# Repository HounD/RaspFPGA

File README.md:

RaspFPGA
========

RaspFPGA mezzanine board for Raspberry Pi

It's not mine, but saved from here for the future use:
http://mbecho.blogspot.it/2013/09/raspfpga-mezzanine-board-for-raspberry.html

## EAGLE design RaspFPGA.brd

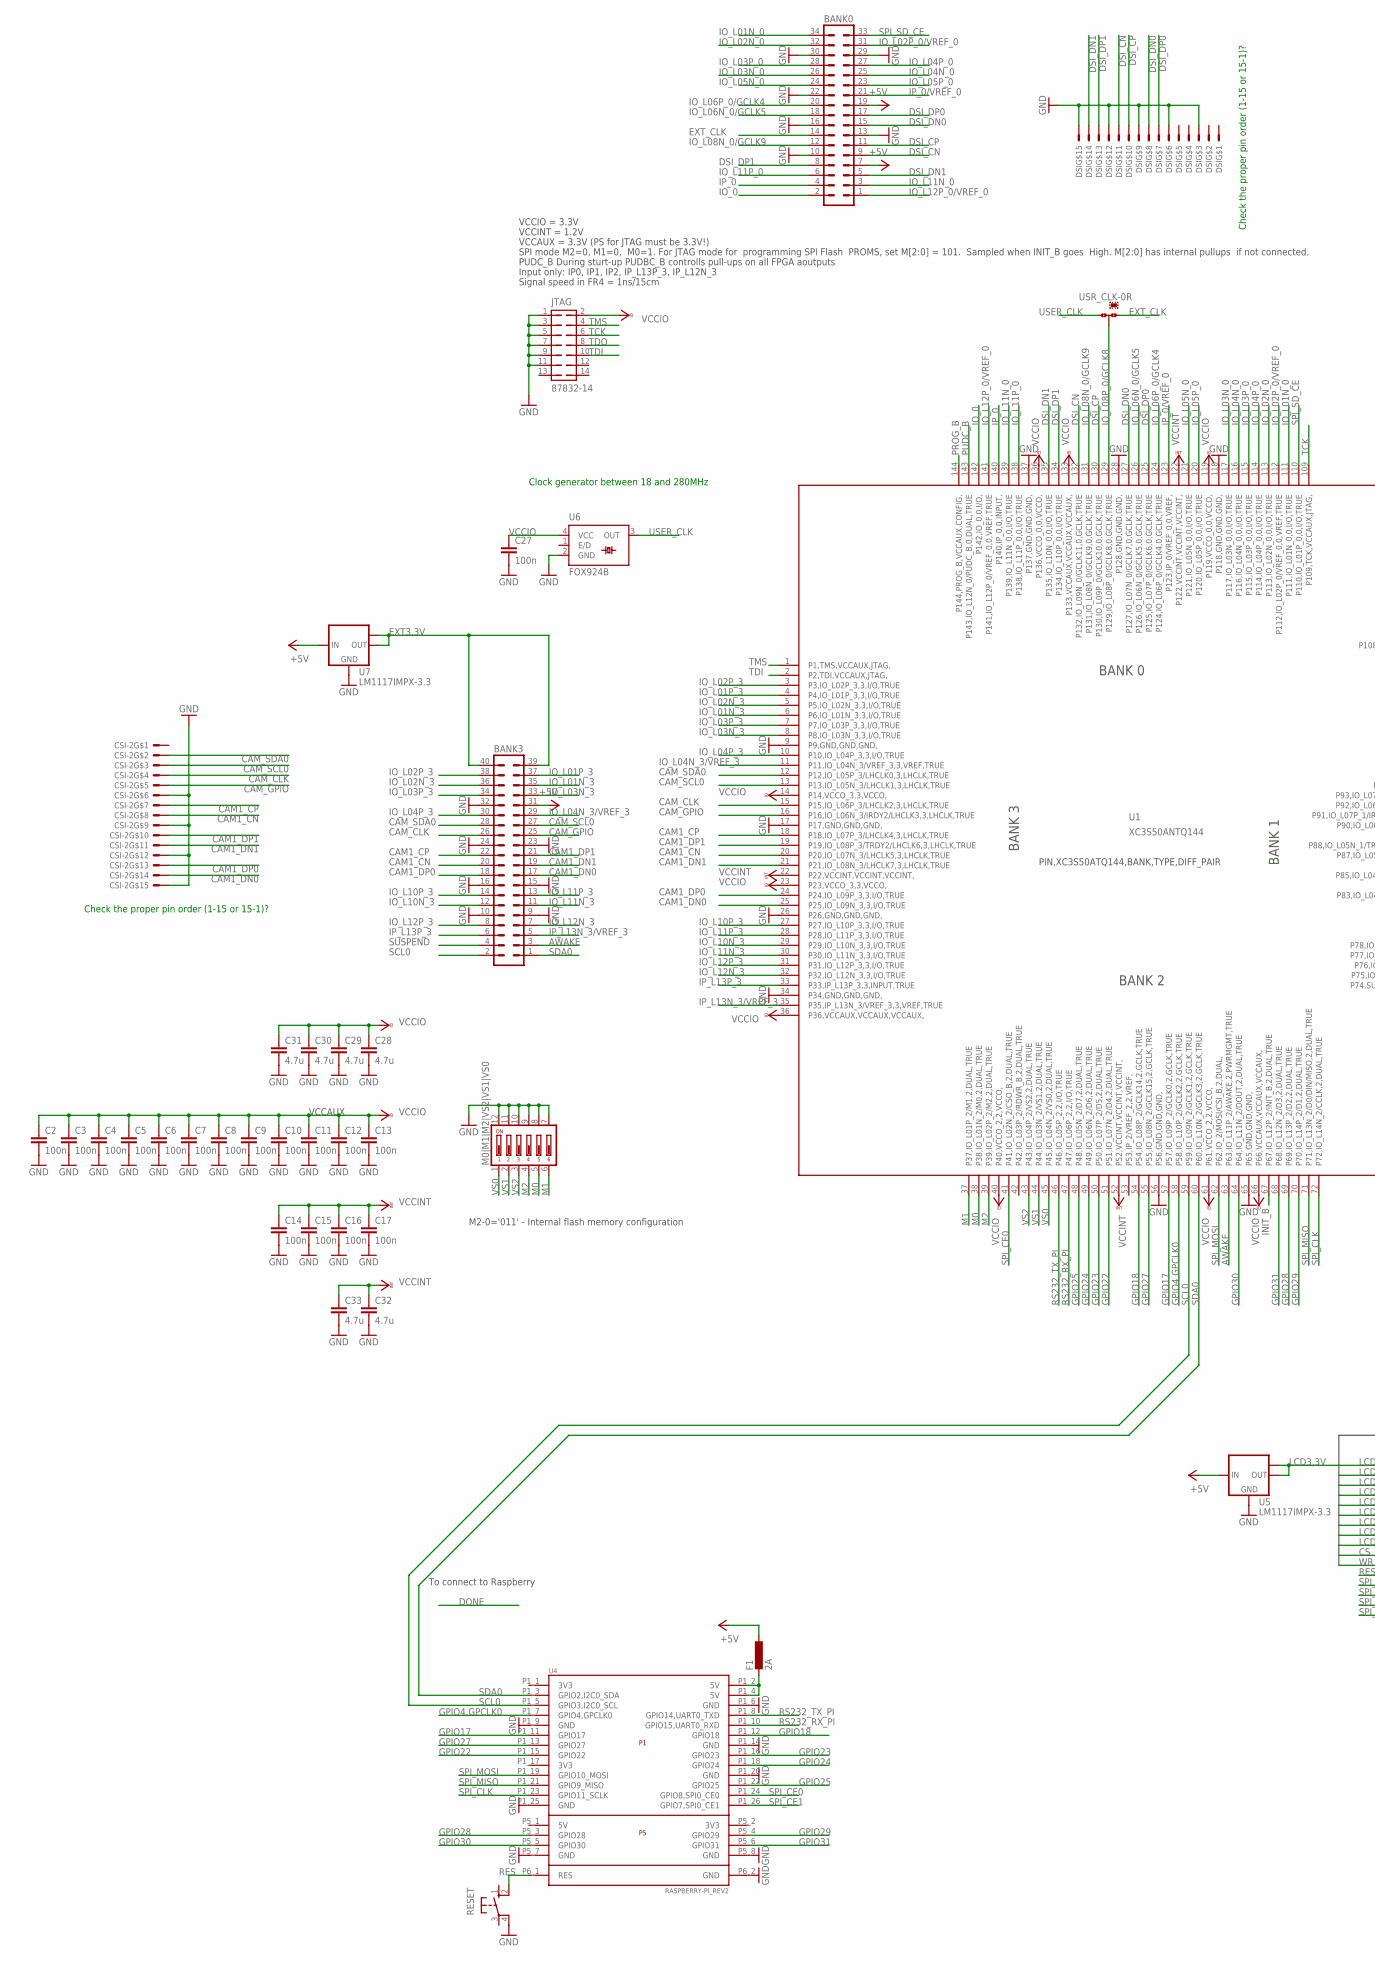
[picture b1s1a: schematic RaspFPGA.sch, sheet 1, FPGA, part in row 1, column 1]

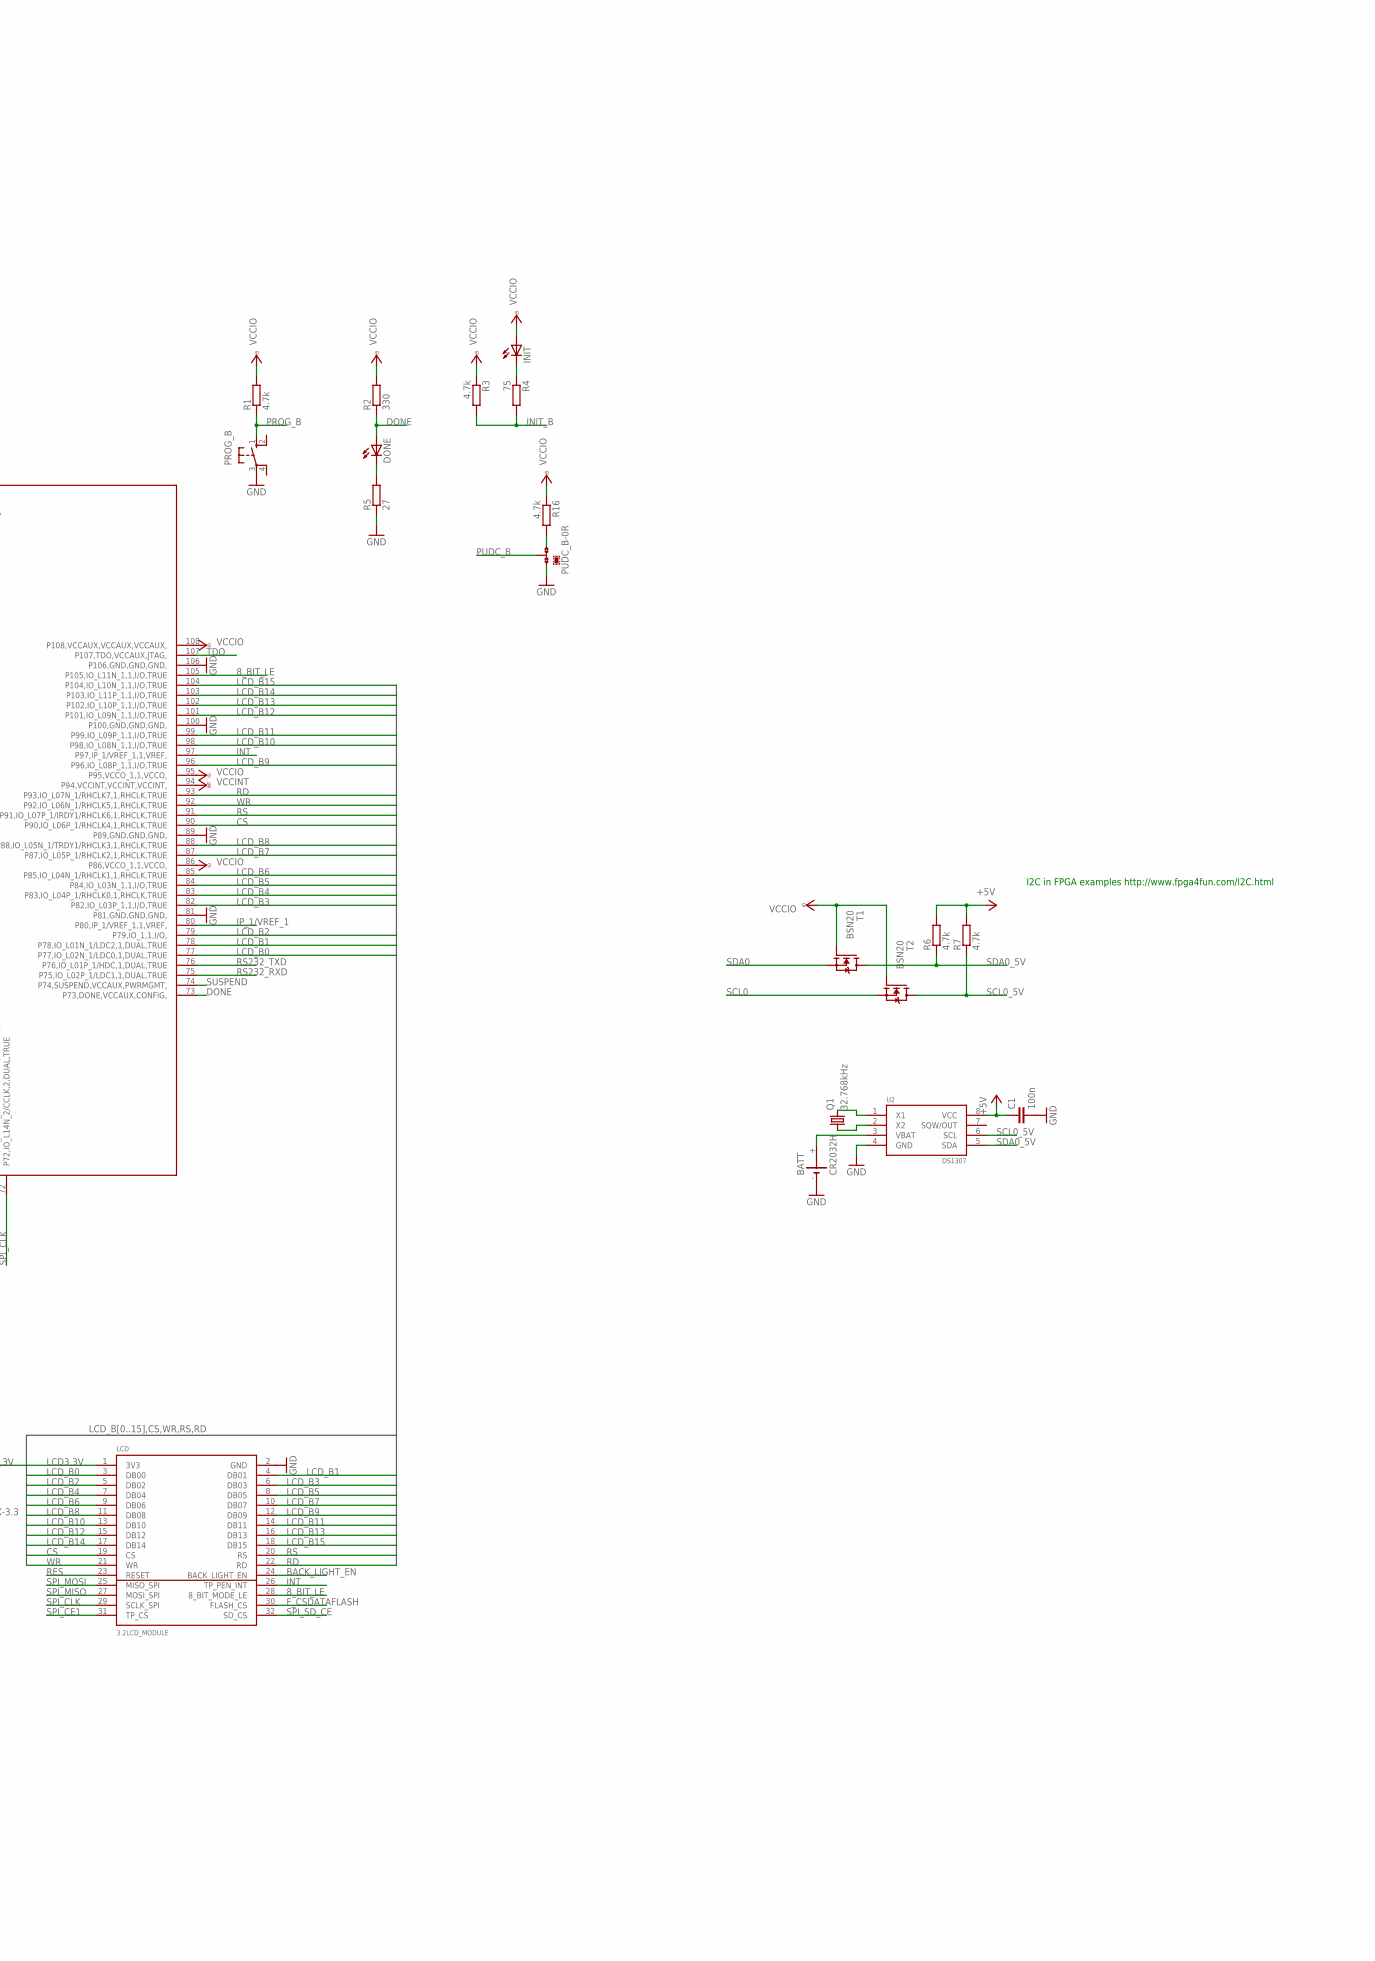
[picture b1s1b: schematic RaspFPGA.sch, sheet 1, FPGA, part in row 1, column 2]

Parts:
BANK0: MA17-2W
BANK3: MA20-2W
BATT: CR2032H
C1, C2, C3, C4, C5, C6, C7, C8, C9, C10, C11, C12, C13, C14, C15, C16, C17, C27: 100n; C0603
C28, C29, C30, C31, C32, C33: 4.7u; C0603
CSI-2: 52271-1579
DONE: LEDCHIP-LED0603; CHIP-LED0603
DSI: 52271-1579
F1: 2A; L1812
INIT: LEDCHIP-LED0603; CHIP-LED0603
JTAG: 87832-14
LCD: 3.2LCD_MODULE
M0|M1|M2|VS2|VS1|VS0: DIP06YL
PROG_B: 10-XX; B3F-10XX
PUDC_B: 0R-JUMPA; A0R-JMP
Q1: 32.768kHz; TC38H
R1, R3, R6, R7, R16: 4.7k; R0603
R2: 330; R0603
R4: 75; R0603
R5: 27; R0603
RESET: 10-XX; B3F-10XX
T1, T2: BSN20; SOT23
U1: XC3S50ANTQ144; TQ144
U2: DS1307; SO8
U4: RASPBERRY-PI_REV2
U5, U7: LM1117IMPX-3.3; SOT223
U6: FOX924B
USR_CLK: 0R-JUMPA; A0R-JMP

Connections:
8_BIT_LE: LCD.28 (8_BIT_MODE_LE), U1.105 (P105,IO_L11N_1,1,I/O,TRUE)
+5V: BANK0.7, BANK0.19, BANK3.31, C1.1, F1.1, R6.2, R7.2, U2.8 (VCC), U5.3 (IN), U7.3 (IN); also elsewhere on the board
AWAKE: BANK3.3, U1.63 (P63,IO_L11P_2/AWAKE,2,PWRMGMT,TRUE)
BACK_LIGHT_EN: LCD.24 (BACK_LIGHT_EN)
CAM1_CN: BANK3.20, CSI-2.P$8, U1.20 (P20,IO_L07N_3/LHCLK5,3,LHCLK,TRUE)
CAM1_CP: BANK3.22, CSI-2.P$7, U1.18 (P18,IO_L07P_3/LHCLK4,3,LHCLK,TRUE)
CAM1_DN0: BANK3.17, CSI-2.P$14, U1.25 (P25,IO_L09N_3,3,I/O,TRUE)
CAM1_DN1: BANK3.19, CSI-2.P$11, U1.21 (P21,IO_L08N_3/LHCLK7,3,LHCLK,TRUE)
CAM1_DP0: BANK3.18, CSI-2.P$13, U1.24 (P24,IO_L09P_3,3,I/O,TRUE)
CAM1_DP1: BANK3.21, CSI-2.P$10, U1.19 (P19,IO_L08P_3/TRDY2/LHCLK6,3,LHCLK,TRUE)
CAM_CLK: BANK3.26, CSI-2.P$4, U1.15 (P15,IO_L06P_3/LHCLK2,3,LHCLK,TRUE)
CAM_GPIO: BANK3.25, CSI-2.P$5, U1.16 (P16,IO_L06N_3/IRDY2/LHCLK3,3,LHCLK,TRUE)
CAM_SCL0: BANK3.27, CSI-2.P$3, U1.13 (P13,IO_L05N_3/LHCLK1,3,LHCLK,TRUE)
CAM_SDA0: BANK3.28, CSI-2.P$2, U1.12 (P12,IO_L05P_3/LHCLK0,3,LHCLK,TRUE)
CS: LCD.19 (CS), U1.90 (P90,IO_L06P_1/RHCLK4,1,RHCLK,TRUE)
DONE: DONE.A, R2.1, U1.73 (P73,DONE,VCCAUX,CONFIG,)
DSI_CN: BANK0.9, DSI.P$11, U1.132 (P132,IO_L09N_0/GCLK11,0,GCLK,TRUE)
DSI_CP: BANK0.11, DSI.P$10, U1.130 (P130,IO_L09P_0/GCLK10,0,GCLK,TRUE)
DSI_DN0: BANK0.15, DSI.P$8, U1.127 (P127,IO_L07N_0/GCLK7,0,GCLK,TRUE)
DSI_DN1: BANK0.5, DSI.P$14, U1.135 (P135,IO_L10N_0,0,I/O,TRUE)
DSI_DP0: BANK0.17, DSI.P$7, U1.125 (P125,IO_L07P_0/GCLK6,0,GCLK,TRUE)
DSI_DP1: BANK0.8, DSI.P$13, U1.134 (P134,IO_L10P_0,0,I/O,TRUE)
EXT3,3V: BANK3.39, BANK3.40, U7.2 (OUT), U7.TAB (OUT1)
EXT_CLK: BANK0.14, USR_CLK.1
F_CSDATAFLASH: LCD.30 (FLASH_CS)
GND: BANK0.10, BANK0.13, BANK0.16, BANK0.22, BANK0.29, BANK0.30, BANK3.9, BANK3.10, BANK3.15, BANK3.16, BANK3.23, BANK3.24, BANK3.32, BATT.-, C1.2, C2.2, C3.2, C4.2, C5.2, C6.2, C7.2, C8.2, C9.2, C10.2, C11.2, C12.2, C13.2, C14.2, C15.2, C16.2, C17.2, C27.2, C28.2, C29.2, C30.2, C31.2, C32.2, C33.2, CSI-2.P$6, CSI-2.P$9, CSI-2.P$12, CSI-2.P$15, DSI.P$3, DSI.P$6, DSI.P$9, DSI.P$12, DSI.P$15, JTAG.1, JTAG.3, JTAG.5, JTAG.7, JTAG.9, JTAG.11, LCD.2 (GND), M0|M1|M2|VS2|VS1|VS0.7, M0|M1|M2|VS2|VS1|VS0.8, M0|M1|M2|VS2|VS1|VS0.9, M0|M1|M2|VS2|VS1|VS0.10, M0|M1|M2|VS2|VS1|VS0.11, M0|M1|M2|VS2|VS1|VS0.12, PROG_B.3, PUDC_B.1, R5.1, RESET.4 (P1), U1.9 (P9,GND,GND,GND,), U1.17 (P17,GND,GND,GND,), U1.26 (P26,GND,GND,GND,), U1.34 (P34,GND,GND,GND,), U1.56 (P56,GND,GND,GND,), U1.65 (P65,GND,GND,GND,), U1.81 (P81,GND,GND,GND,), U1.89 (P89,GND,GND,GND,), U1.100 (P100,GND,GND,GND,), U1.106 (P106,GND,GND,GND,), U1.118 (P118,GND,GND,GND,), U1.128 (P128,GND,GND,GND,), U1.137 (P137,GND,GND,GND,), U2.4 (GND), U4.P1_6 (GND), U4.P1_9 (GND), U4.P1_14 (GND), U4.P1_20 (GND), U4.P1_25 (GND), U4.P5_7 (GND), U4.P5_8 (GND), U4.P6_2 (GND), U5.1 (GND), U6.2 (GND), U7.1 (GND); also elsewhere on the board
GPIO4,GPCLK0: U1.58 (P58,IO_L10P_2/GCLK2,2,GCLK,TRUE), U4.P1_7 (GPIO4,GPCLK0)
GPIO17: U1.57 (P57,IO_L09P_2/GCLK0,2,GCLK,TRUE), U4.P1_11 (GPIO17)
GPIO18: U1.54 (P54,IO_L08P_2/GCLK14,2,GCLK,TRUE), U4.P1_12 (GPIO18)
GPIO22: U1.51 (P51,IO_L07N_2/D4,2,DUAL,TRUE), U4.P1_15 (GPIO22)
GPIO23: U1.50 (P50,IO_L07P_2/D5,2,DUAL,TRUE), U4.P1_16 (GPIO23)
GPIO24: U1.49 (P49,IO_L06N_2/D6,2,DUAL,TRUE), U4.P1_18 (GPIO24)
GPIO25: U1.48 (P48,IO_L05N_2/D7,2,DUAL,TRUE), U4.P1_22 (GPIO25)
GPIO27: U1.55 (P55,IO_L08N_2/GCLK15,2,GCLK,TRUE), U4.P1_13 (GPIO27)
GPIO28: U1.69 (P69,IO_L13P_2/D2,2,DUAL,TRUE), U4.P5_3 (GPIO28)
GPIO29: U1.70 (P70,IO_L14P_2/D1,2,DUAL,TRUE), U4.P5_4 (GPIO29)
GPIO30: U1.64 (P64,IO_L11N_2/DOUT,2,DUAL,TRUE), U4.P5_5 (GPIO30)
GPIO31: U1.68 (P68,IO_L12N_2/D3,2,DUAL,TRUE), U4.P5_6 (GPIO31)
INIT: INIT.C, R4.1
INIT_B: R3.2, R4.2, U1.67 (P67,IO_L12P_2/INIT_B,2,DUAL,TRUE)
INT: LCD.26 (TP_PEN_INT), U1.97 (P97,IP_1/VREF_1,1,VREF,)
IO_0: BANK0.2, U1.142 (P142,IO_0,0,I/O,)
IO_L01N_0: BANK0.34, U1.111 (P111,IO_L01N_0,0,I/O,TRUE)
IO_L01N_3: BANK3.35, U1.6 (P6,IO_L01N_3,3,I/O,TRUE)
IO_L01P_3: BANK3.37, U1.4 (P4,IO_L01P_3,3,I/O,TRUE)
IO_L02N_0: BANK0.32, U1.113 (P113,IO_L02N_0,0,I/O,TRUE)
IO_L02N_3: BANK3.36, U1.5 (P5,IO_L02N_3,3,I/O,TRUE)
IO_L02P_0/VREF_0: BANK0.31, U1.112 (P112,IO_L02P_0/VREF_0,0,VREF,TRUE)
IO_L02P_3: BANK3.38, U1.3 (P3,IO_L02P_3,3,I/O,TRUE)
IO_L03N_0: BANK0.26, U1.117 (P117,IO_L03N_0,0,I/O,TRUE)
IO_L03N_3: BANK3.33, U1.8 (P8,IO_L03N_3,3,I/O,TRUE)
IO_L03P_0: BANK0.28, U1.115 (P115,IO_L03P_0,0,I/O,TRUE)
IO_L03P_3: BANK3.34, U1.7 (P7,IO_L03P_3,3,I/O,TRUE)
IO_L04N_0: BANK0.25, U1.116 (P116,IO_L04N_0,0,I/O,TRUE)
IO_L04N_3/VREF_3: BANK3.29, U1.11 (P11,IO_L04N_3/VREF_3,3,VREF,TRUE)
IO_L04P_0: BANK0.27, U1.114 (P114,IO_L04P_0,0,I/O,TRUE)
IO_L04P_3: BANK3.30, U1.10 (P10,IO_L04P_3,3,I/O,TRUE)
IO_L05N_0: BANK0.24, U1.121 (P121,IO_L05N_0,0,I/O,TRUE)
IO_L05P_0: BANK0.23, U1.120 (P120,IO_L05P_0,0,I/O,TRUE)
IO_L06N_0/GCLK5: BANK0.18, U1.126 (P126,IO_L06N_0/GCLK5,0,GCLK,TRUE)
IO_L06P_0/GCLK4: BANK0.20, U1.124 (P124,IO_L06P_0/GCLK4,0,GCLK,TRUE)
IO_L08N_0/GCLK9: BANK0.12, U1.131 (P131,IO_L08N_0/GCLK9,0,GCLK,TRUE)
IO_L08P_0/GCLK8: U1.129 (P129,IO_L08P_0/GCLK8,0,GCLK,TRUE), USR_CLK.2
IO_L10N_3: BANK3.12, U1.29 (P29,IO_L10N_3,3,I/O,TRUE)
IO_L10P_3: BANK3.14, U1.27 (P27,IO_L10P_3,3,I/O,TRUE)
IO_L11N_0: BANK0.3, U1.139 (P139,IO_L11N_0,0,I/O,TRUE)
IO_L11N_3: BANK3.11, U1.30 (P30,IO_L11N_3,3,I/O,TRUE)
IO_L11P_0: BANK0.6, U1.138 (P138,IO_L11P_0,0,I/O,TRUE)
IO_L11P_3: BANK3.13, U1.28 (P28,IO_L11P_3,3,I/O,TRUE)
IO_L12N_3: BANK3.7, U1.32 (P32,IO_L12N_3,3,I/O,TRUE)
IO_L12P_0/VREF_0: BANK0.1, U1.141 (P141,IO_L12P_0/VREF_0,0,VREF,TRUE)
IO_L12P_3: BANK3.8, U1.31 (P31,IO_L12P_3,3,I/O,TRUE)
IP_0: BANK0.4, U1.140 (P140,IP_0,0,INPUT,)
IP_0/VREF_0: BANK0.21, U1.123 (P123,IP_0/VREF_0,0,VREF,)
IP_1/VREF_1: U1.80 (P80,IP_1/VREF_1,1,VREF,)
IP_L13N_3/VREF_3: BANK3.5, U1.35 (P35,IP_L13N_3/VREF_3,3,VREF,TRUE)
IP_L13P_3: BANK3.6, U1.33 (P33,IP_L13P_3,3,INPUT,TRUE)
LCD3,3V: LCD.1 (3V3), U5.2 (OUT), U5.TAB (OUT1)
LCD_B0: LCD.3 (DB00), U1.77 (P77,IO_L02N_1/LDC0,1,DUAL,TRUE)
LCD_B1: LCD.4 (DB01), U1.78 (P78,IO_L01N_1/LDC2,1,DUAL,TRUE)
LCD_B2: LCD.5 (DB02), U1.79 (P79,IO_1,1,I/O,)
LCD_B3: LCD.6 (DB03), U1.82 (P82,IO_L03P_1,1,I/O,TRUE)
LCD_B4: LCD.7 (DB04), U1.83 (P83,IO_L04P_1/RHCLK0,1,RHCLK,TRUE)
LCD_B5: LCD.8 (DB05), U1.84 (P84,IO_L03N_1,1,I/O,TRUE)
LCD_B6: LCD.9 (DB06), U1.85 (P85,IO_L04N_1/RHCLK1,1,RHCLK,TRUE)
LCD_B7: LCD.10 (DB07), U1.87 (P87,IO_L05P_1/RHCLK2,1,RHCLK,TRUE)
LCD_B8: LCD.11 (DB08), U1.88 (P88,IO_L05N_1/TRDY1/RHCLK3,1,RHCLK,TRUE)
LCD_B9: LCD.12 (DB09), U1.96 (P96,IO_L08P_1,1,I/O,TRUE)
LCD_B10: LCD.13 (DB10), U1.98 (P98,IO_L08N_1,1,I/O,TRUE)
LCD_B11: LCD.14 (DB11), U1.99 (P99,IO_L09P_1,1,I/O,TRUE)
LCD_B12: LCD.15 (DB12), U1.101 (P101,IO_L09N_1,1,I/O,TRUE)
LCD_B13: LCD.16 (DB13), U1.102 (P102,IO_L10P_1,1,I/O,TRUE)
LCD_B14: LCD.17 (DB14), U1.103 (P103,IO_L11P_1,1,I/O,TRUE)
LCD_B15: LCD.18 (DB15), U1.104 (P104,IO_L10N_1,1,I/O,TRUE)
M0: M0|M1|M2|VS2|VS1|VS0.5, U1.38 (P38,IO_L01N_2/M0,2,DUAL,TRUE)
M1: M0|M1|M2|VS2|VS1|VS0.6, U1.37 (P37,IO_L01P_2/M1,2,DUAL,TRUE)
M2: M0|M1|M2|VS2|VS1|VS0.4, U1.39 (P39,IO_L02P_2/M2,2,DUAL,TRUE)
unnamed: F1.2, U4.P1_2 (5V), U4.P1_4 (5V)
unnamed: DONE.C, R5.2
unnamed: PUDC_B.3, R16.2
unnamed: Q1.1, U2.2 (X2)
unnamed: Q1.2, U2.1 (X1)
unnamed: BATT.+, U2.3 (VBAT)
PROG_B: PROG_B.1 (S), R1.1, U1.144 (P144,PROG_B,VCCAUX,CONFIG,)
PUDC_B: PUDC_B.2, U1.143 (P143,IO_L12N_0/PUDC_B,0,DUAL,TRUE)
RD: LCD.22 (RD), U1.93 (P93,IO_L07N_1/RHCLK7,1,RHCLK,TRUE)
RES: LCD.23 (RESET), RESET.2 (S1), U4.P6_1 (RES)
RS: LCD.20 (RS), U1.91 (P91,IO_L07P_1/IRDY1/RHCLK6,1,RHCLK,TRUE)
RS232_RXD: U1.75 (P75,IO_L02P_1/LDC1,1,DUAL,TRUE); also elsewhere on the board
RS232_RX_PI: U1.47 (P47,IO_L06P_2,2,I/O,TRUE), U4.P1_10 (GPIO15,UART0_RXD)
RS232_TXD: U1.76 (P76,IO_L01P_1/HDC,1,DUAL,TRUE); also elsewhere on the board
RS232_TX_PI: U1.46 (P46,IO_L05P_2,2,I/O,TRUE), U4.P1_8 (GPIO14,UART0_TXD)
SCL0: BANK3.2, T2.2 (S), U1.59 (P59,IO_L09N_2/GCLK1,2,GCLK,TRUE), U4.P1_5 (GPIO3,I2C0_SCL)
SCL0_5V: R7.1, T2.3 (D), U2.6 (SCL)
SDA0: BANK3.1, T1.2 (S), U1.60 (P60,IO_L10N_2/GCLK3,2,GCLK,TRUE), U4.P1_3 (GPIO2,I2C0_SDA)
SDA0_5V: R6.1, T1.3 (D), U2.5 (SDA)
SPI_CE0: U1.41 (P41,IO_L02N_2/CSO_B,2,DUAL,TRUE), U4.P1_24 (GPIO8,SPI0_CE0)
SPI_CE1: LCD.31 (TP_CS), U4.P1_26 (GPIO7,SPI0_CE1)
SPI_CLK: LCD.29 (SCLK_SPI), U1.72 (P72,IO_L14N_2/CCLK,2,DUAL,TRUE), U4.P1_23 (GPIO11_SCLK)
SPI_MISO: LCD.27 (MOSI_SPI), U1.71 (P71,IO_L13N_2/D0/DIN/MISO,2,DUAL,TRUE), U4.P1_21 (GPIO9_MISO)
SPI_MOSI: LCD.25 (MISO_SPI), U1.62 (P62,IO_2/MOSI/CSI_B,2,DUAL,), U4.P1_19 (GPIO10_MOSI)
SPI_SD_CE: BANK0.33, LCD.32 (SD_CS), U1.110 (P110,IO_L01P_0,0,I/O,TRUE)
SUSPEND: BANK3.4, U1.74 (P74,SUSPEND,VCCAUX,PWRMGMT,)
TCK: JTAG.6, U1.109 (P109,TCK,VCCAUX,JTAG,)
TDI: JTAG.10, U1.2 (P2,TDI,VCCAUX,JTAG,)
TDO: JTAG.8, U1.107 (P107,TDO,VCCAUX,JTAG,)
TMS: JTAG.4, U1.1 (P1,TMS,VCCAUX,JTAG,)
USER_CLK: U6.3 (OUT), USR_CLK.3
VCCINT: C14.1, C15.1, C16.1, C17.1, C32.1, C33.1, U1.22 (P22,VCCINT,VCCINT,VCCINT,), U1.52 (P52,VCCINT,VCCINT,VCCINT,), U1.94 (P94,VCCINT,VCCINT,VCCINT,), U1.122 (P122,VCCINT,VCCINT,VCCINT,); also elsewhere on the board
VCCIO: C2.1, C3.1, C4.1, C5.1, C6.1, C7.1, C8.1, C9.1, C10.1, C11.1, C12.1, C13.1, C27.1, C28.1, C29.1, C30.1, C31.1, INIT.A, JTAG.2, R1.2, R2.2, R3.1, R16.1, T1.1 (G), T2.1 (G), U1.14 (P14,VCCO_3,3,VCCO,), U1.23 (P23,VCCO_3,3,VCCO,), U1.36 (P36,VCCAUX,VCCAUX,VCCAUX,), U1.40 (P40,VCCO_2,2,VCCO,), U1.61 (P61,VCCO_2,2,VCCO,), U1.66 (P66,VCCAUX,VCCAUX,VCCAUX,), U1.86 (P86,VCCO_1,1,VCCO,), U1.95 (P95,VCCO_1,1,VCCO,), U1.108 (P108,VCCAUX,VCCAUX,VCCAUX,), U1.119 (P119,VCCO_0,0,VCCO,), U1.133 (P133,VCCAUX,VCCAUX,VCCAUX,), U1.136 (P136,VCCO_0,0,VCCO,), U6.4 (VCC); also elsewhere on the board
VS0: M0|M1|M2|VS2|VS1|VS0.1, U1.45 (P45,IO_L04N_2/VS0,2,DUAL,TRUE)
VS1: M0|M1|M2|VS2|VS1|VS0.2, U1.44 (P44,IO_L03N_2/VS1,2,DUAL,TRUE)
VS2: M0|M1|M2|VS2|VS1|VS0.3, U1.43 (P43,IO_L04P_2/VS2,2,DUAL,TRUE)
WR: LCD.21 (WR), U1.92 (P92,IO_L06N_1/RHCLK5,1,RHCLK,TRUE)

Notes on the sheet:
PIN,XC3S50ATQ144,BANK,TYPE,DIFF_PAIR
VCCIO = 3.3V
VCCINT = 1.2V
SPI mode M2=0, M1=0, M0=1. For JTAG mode for programming SPI Flash PROMS, set M[2:0] = 101. Sampled when INIT_B goes High. M[2:0] has internal pullups if not connected.
PUDC_B During sturt-up PUDBC_B controlls pull-ups on all FPGA aoutputs
Input only: IP0, IP1, IP2, IP_L13P_3, IP_L12N_3
To connect to Raspberry
VCCAUX = 3.3V (PS for JTAG must be 3.3V!)
VCCAUX
I2C in FPGA examples http://www.fpga4fun.com/I2C.html
Clock generator between 18 and 280MHz
Signal speed in FR4 = 1ns/15cm
Check the proper pin order (1-15 or 15-1)?
M2-0='011' - Internal flash memory configuration

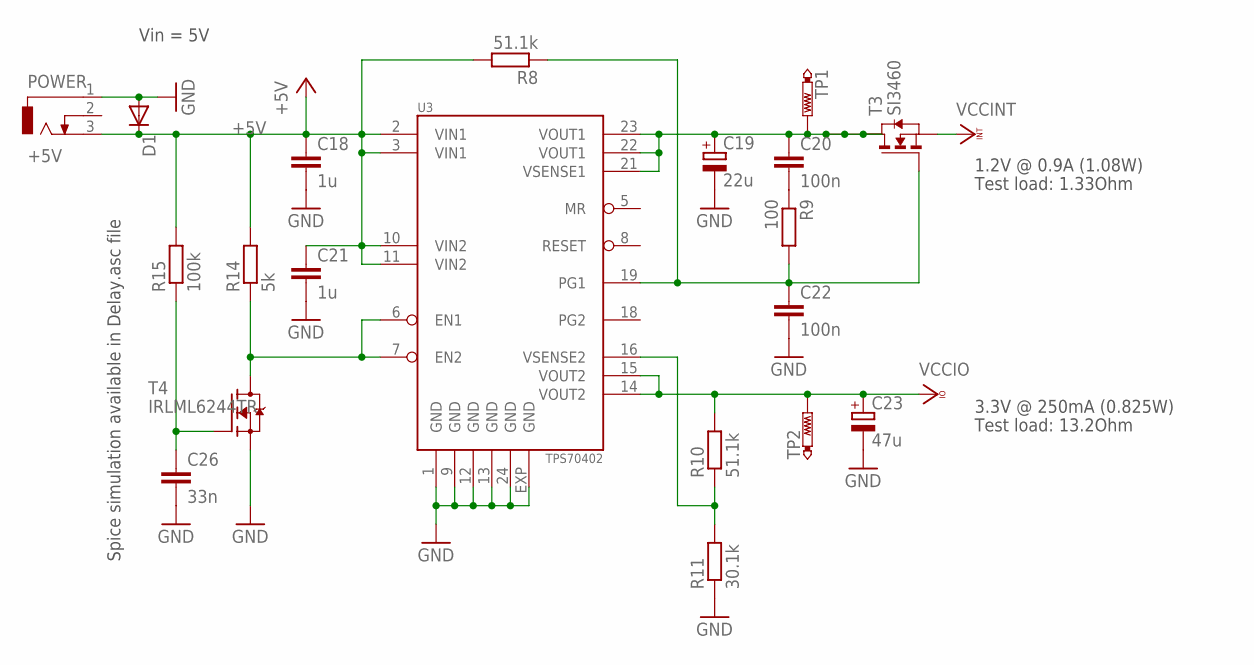
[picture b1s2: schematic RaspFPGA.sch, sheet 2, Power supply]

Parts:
C18, C21: 1u; C1206
C19: 22u; PANASONIC_F
C20, C22: 100n; C0603
C23: 47u; PANASONIC_F
C26: 33n; C0603
D1: DIODE-DO-214AC; DO-214AC
POWER: +5V; DCJ0202
R8, R10: 51.1k; R0603
R9: 100; R0603
R11: 30.1k; R0603
R14: 5k; R0603
R15: 100k; R0603
T3: SI3460; SOT23-6
T4: IRLML6244TR; SOT23
TP1, TP2: PTR1B1,27; B1,27
U3: TPS70402; HTSSOP24PWP

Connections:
+5V: C18.1, C21.1, D1.C, POWER.3, R8.2, R14.2, R15.2, U3.2 (VIN1), U3.3 (VIN1), U3.10 (VIN2), U3.11 (VIN2); also elsewhere on the board
GND: C18.2, C19.-, C21.2, C22.2, C23.-, C26.2, D1.A, POWER.1, R11.1, T4.2 (S), U3.1 (GND), U3.9 (GND), U3.12 (GND), U3.13 (GND), U3.24 (GND), U3.EXP (GND); also elsewhere on the board
unnamed: R14.1, T4.3 (D), U3.6 (EN1), U3.7 (EN2)
unnamed: C26.1, R15.1, T4.1 (G)
unnamed: C22.1, R8.1, R9.2, T3.3 (G), U3.19 (PG1)
unnamed: R10.1, R11.2, U3.16 (VSENSE2)
unnamed: C20.2, R9.1
T1: C19.+, C20.1, T3.1 (D1), T3.2 (D2), T3.5 (D3), T3.6 (D), TP1.PP, U3.21 (VSENSE1), U3.22 (VOUT1), U3.23 (VOUT1)
VCCINT: T3.4 (S); also elsewhere on the board
VCCIO: C23.+, R10.2, TP2.PP, U3.14 (VOUT2), U3.15 (VOUT2); also elsewhere on the board

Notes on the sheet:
3.3V @ 250mA (0.825W)
1.2V @ 0.9A (1.08W)
Vin = 5V
Spice simulation available in Delay.asc file
Test load: 1.33Ohm
Test load: 13.2Ohm

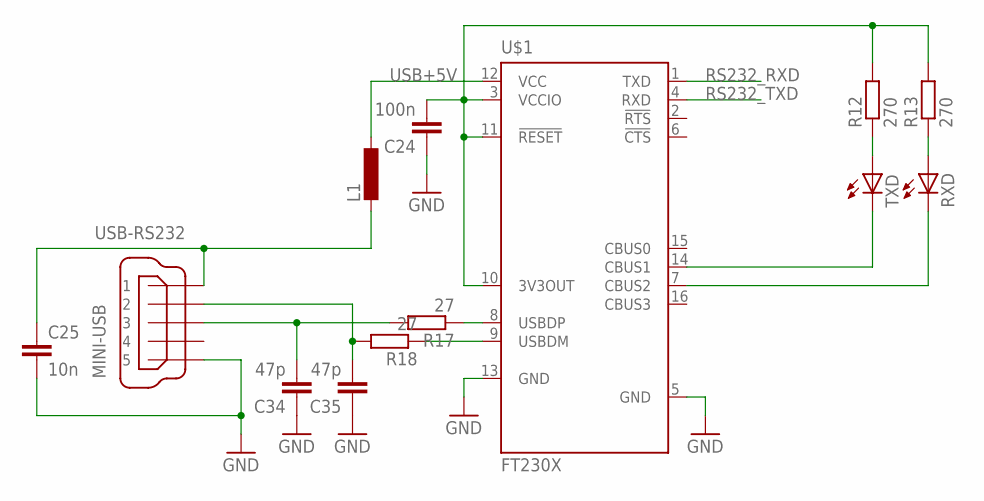
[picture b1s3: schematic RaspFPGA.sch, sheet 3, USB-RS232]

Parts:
C24: 100n; C0603
C25: 10n; C0603
C34, C35: 47p; C0603
L1: L-EUL2012C; L2012C
R12, R13: 270; R0603
R17, R18: 27; R0603
RXD: LEDCHIP-LED0805; CHIP-LED0805
TXD: LEDCHIP-LED0805; CHIP-LED0805
U$1: FT230X; SSOP16
USB-RS232: MINI-USB; 32005-201

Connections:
FT232_VCCIO: C24.2, R12.2, R13.2, U$1.3 (VCCIO), U$1.10 (3V3OUT), U$1.11 (!RESET)
GND: C24.1, C25.2, C34.1, C35.1, U$1.5 (GND), U$1.13 (GND), USB-RS232.5; also elsewhere on the board
unnamed: C25.1, L1.2, USB-RS232.1
unnamed: R12.1, TXD.A
unnamed: R13.1, RXD.A
unnamed: TXD.C, U$1.14 (CBUS1)
unnamed: RXD.C, U$1.7 (CBUS2)
RS232_RXD: U$1.1 (TXD); also elsewhere on the board
RS232_TXD: U$1.4 (RXD); also elsewhere on the board
USB+5V: L1.1, U$1.12 (VCC)
USBDM: C35.2, R18.2, USB-RS232.2
USBDMF: R18.1, U$1.9 (USBDM)
USBDP: C34.2, R17.2, USB-RS232.3
USBDPF: R17.1, U$1.8 (USBDP)

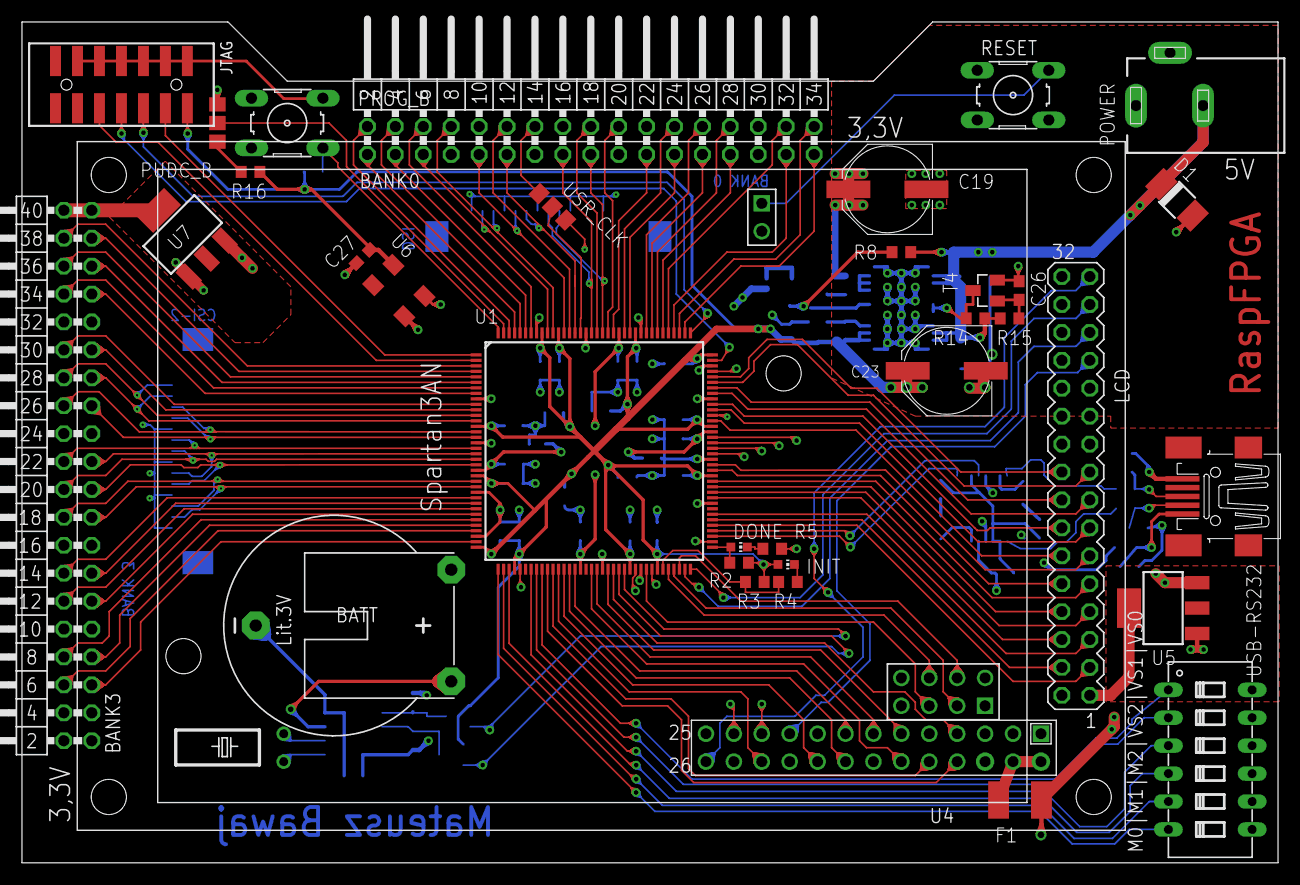
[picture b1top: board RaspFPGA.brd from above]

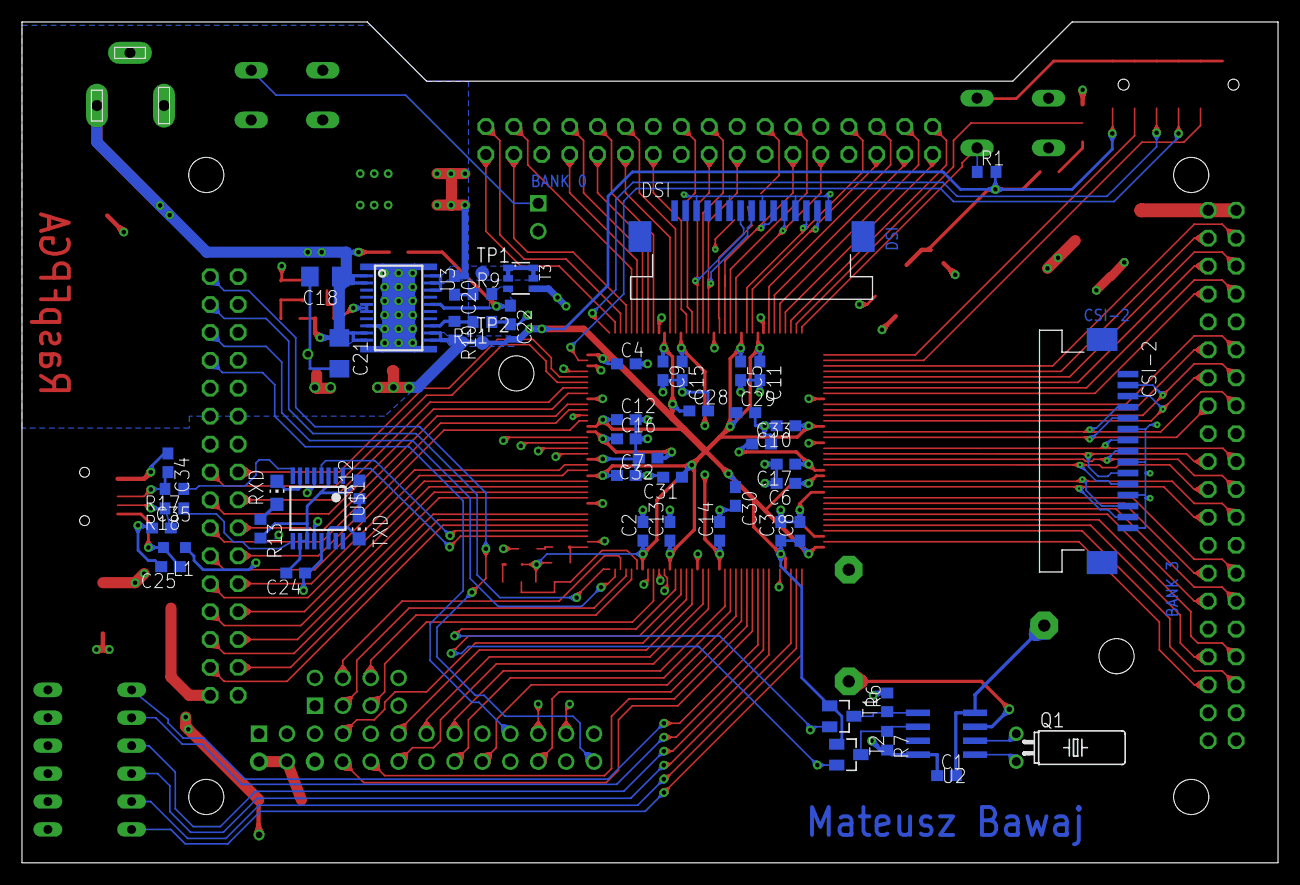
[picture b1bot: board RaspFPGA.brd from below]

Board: 4 copper layers, 114.3 x 76.5 mm, 89 parts (55 on the bottom side), 148 nets.

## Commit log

2013-09-27 Files added
